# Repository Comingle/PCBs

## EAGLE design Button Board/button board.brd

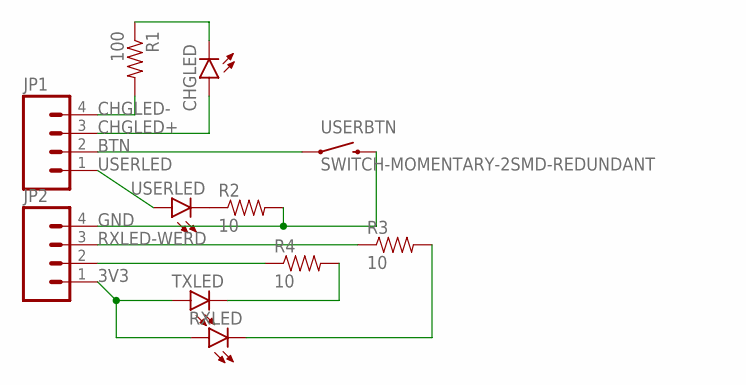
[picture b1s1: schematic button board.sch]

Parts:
CHGLED: LED-FKIT-1206; FKIT-LED-1206
JP1, JP2: M04PTH; 1X04
R1: 100; 0603-RES
R2, R3, R4: 10; 0603-RES
RXLED: LED-FKIT-1206; FKIT-LED-1206
TXLED: LED-FKIT-1206; FKIT-LED-1206
USERBTN: SWITCH-MOMENTARY-2SMD-REDUNDANT; TACTILE-SWITCH-SMD
USERLED: LED-FKIT-1206; FKIT-LED-1206

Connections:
3V3: JP2.1, RXLED.A, TXLED.A
BTN: JP1.2, USERBTN.1, USERBTN.2 (1)
CHGLED+: CHGLED.A, JP1.3
CHGLED-: JP1.4, R1.2
GND: JP2.4, R2.2, USERBTN.3 (2), USERBTN.4 (2)
unnamed: CHGLED.C, R1.1
unnamed: R2.1, USERLED.C
RXLED-: JP2.3, R3.1
RXLED-WERD: R3.2, RXLED.C
TXLED-: JP2.2, R4.1
TXLED-WERD: R4.2, TXLED.C
USERLED: JP1.1, USERLED.A

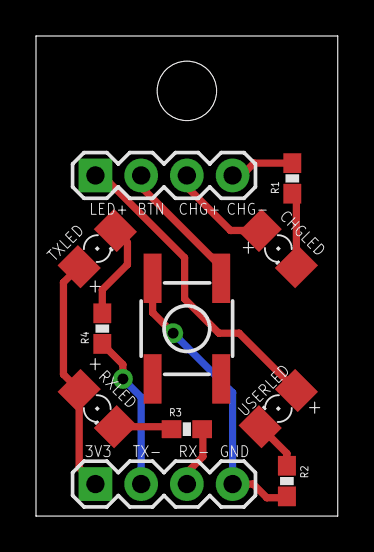
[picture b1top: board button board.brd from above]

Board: 2 copper layers, 16.8 x 26.7 mm, 12 parts (0 on the bottom side), 12 nets.

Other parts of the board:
U$1: STAND-OFF

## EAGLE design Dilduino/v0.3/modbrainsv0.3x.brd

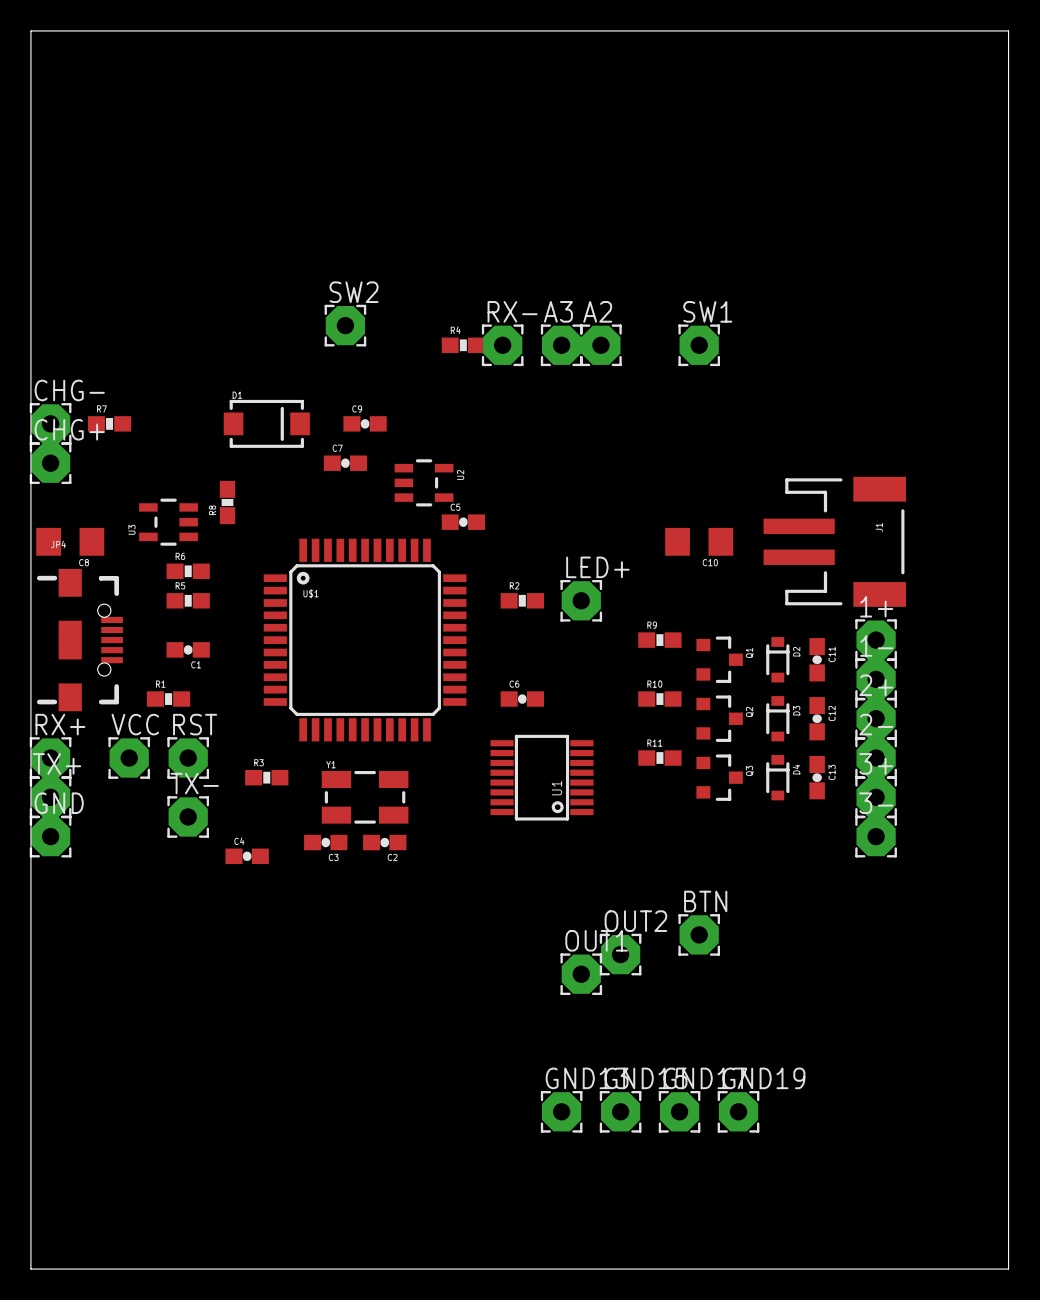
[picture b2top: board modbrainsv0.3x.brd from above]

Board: 2 copper layers, 63.2 x 80.0 mm, 66 parts (0 on the bottom side), 45 nets, no tracks yet.

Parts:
1+, 1-, 2+, 2-, 3+, 3-: 2,54/1,1
A2, A3: 2,54/1,1
BTN: 2,54/1,1
C1: 1.0uF; 0603-CAP
C2, C3: 22pF; 0603-CAP
C4, C5, C6, C11, C12, C13: 0.1uF; 0603-CAP
C7: 4.7uF; 0603-CAP
C8, C10: 4.7uF; 1206
C9: 470pF; 0603-CAP
CHG+: 2,54/1,1
CHG-: 2,54/1,1
D1: B340A; SMA-DIODE
D2, D3: BAT20JFILM; SOD-323
D4: 1N914BWS; SOD-323
FRAME1: FRAME-LETTER; CREATIVE_COMMONS
GND, GND13, GND15, GND17, GND19: 2,54/1,1
J1: JST-2-SMD
JP4: USB; USB-B-MICRO-SMD_V03
LED+: 2,54/1,1
OUT1, OUT2: 2,54/1,1
Q1, Q2, Q3: SOT23-3
R1, R8: 10k; 0603-RES
R2, R3, R4, R7: 430; 0603-RES
R5, R6: 22; 0603-RES
R9, R10, R11: 1k; 0603-RES
RST: 2,54/1,1
RX+: 2,54/1,1
RX-: 2,54/1,1
SW1, SW2: 2,54/1,1
TX+: 2,54/1,1
TX-: 2,54/1,1
U1: 74CBTLV3253; SSOP16-PRACTICE
U2: MIC5219 3.3V; SOT23-5
U3: MCP73831; SOT23-5
U$1: ATMEGA32U4TQFP-44; TQFP44
VCC: 2,54/1,1
Y1: CRYSTAL-SMD-5X3

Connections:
3.3V: RX+.1, TX+.1, U2.5, VCC.1
A7: U1.6, U$1.27
A8: U1.10, U$1.29
BVCC: 1+.1, 2+.1, 3+.1, C10.1, C11.1, C12.1, C13.1, D1.A, D2.C, D3.C, D4.C, J1.2, U3.3
D+: R6.2, U$1.4
D-: R5.2, U$1.3
GND: C1.2, C2.1, C3.1, C4.2, C5.2, C6.2, C7.2, C8.2, C9.2, C10.2, GND.1, GND13.1, GND15.1, GND17.1, GND19.1, J1.1, JP4.GND1, Q1.2, Q2.2, Q3.2, U1.1, U1.8, U1.15, U$1.5, U$1.15, U$1.23, U$1.33, U$1.35, U$1.43
MISO: U1.12, U$1.11
MOTOR1: R9.1, U$1.31
MOTOR2: R10.1, U$1.30
MOTOR3: R11.1, U$1.12
MUX0: U1.14, U$1.28
MUX1: U1.2, U$1.26
unnamed: C2.2, U$1.17, Y1.3
unnamed: C3.2, U$1.16, Y1.1
unnamed: R1.2, RST.1, U$1.13
unnamed: R2.1, U$1.32
unnamed: R4.1, U$1.8
unnamed: R3.1, U$1.22
unnamed: LED+.1, R2.2
unnamed: R4.2, RX-.1
unnamed: R3.2, TX-.1
unnamed: JP4.D+1, R5.1
unnamed: JP4.D-1, R6.1
unnamed: OUT2.1, U1.9
unnamed: OUT1.1, U1.7
unnamed: A2.1, U$1.38
unnamed: A3.1, U$1.39
unnamed: BTN.1, U$1.25
unnamed: R7.1, U3.1
unnamed: CHG-.1, R7.2
unnamed: R8.2, U2.2, U3.2
unnamed: SW2.1, U2.3
unnamed: C9.1, U2.4
unnamed: 1-.1, C11.2, D2.A, Q1.3
unnamed: 2-.1, C12.2, D3.A, Q2.3
unnamed: 3-.1, C13.2, D4.A, Q3.3
unnamed: Q1.1, R9.2
unnamed: Q2.1, R10.2
unnamed: Q3.1, R11.2
SCK: U1.4, U$1.9
SCL: U1.11, U$1.18
SDA: U1.5, U$1.19
UVCC: C8.1, CHG+.1, D1.C, JP4.VBUS1, SW1.1, U2.1, U3.4, U$1.7
VCC: C1.1, C4.1, C5.1, C6.1, C7.1, R1.1, U1.16, U$1.6, U$1.14, U$1.24, U$1.34, U$1.42, U$1.44

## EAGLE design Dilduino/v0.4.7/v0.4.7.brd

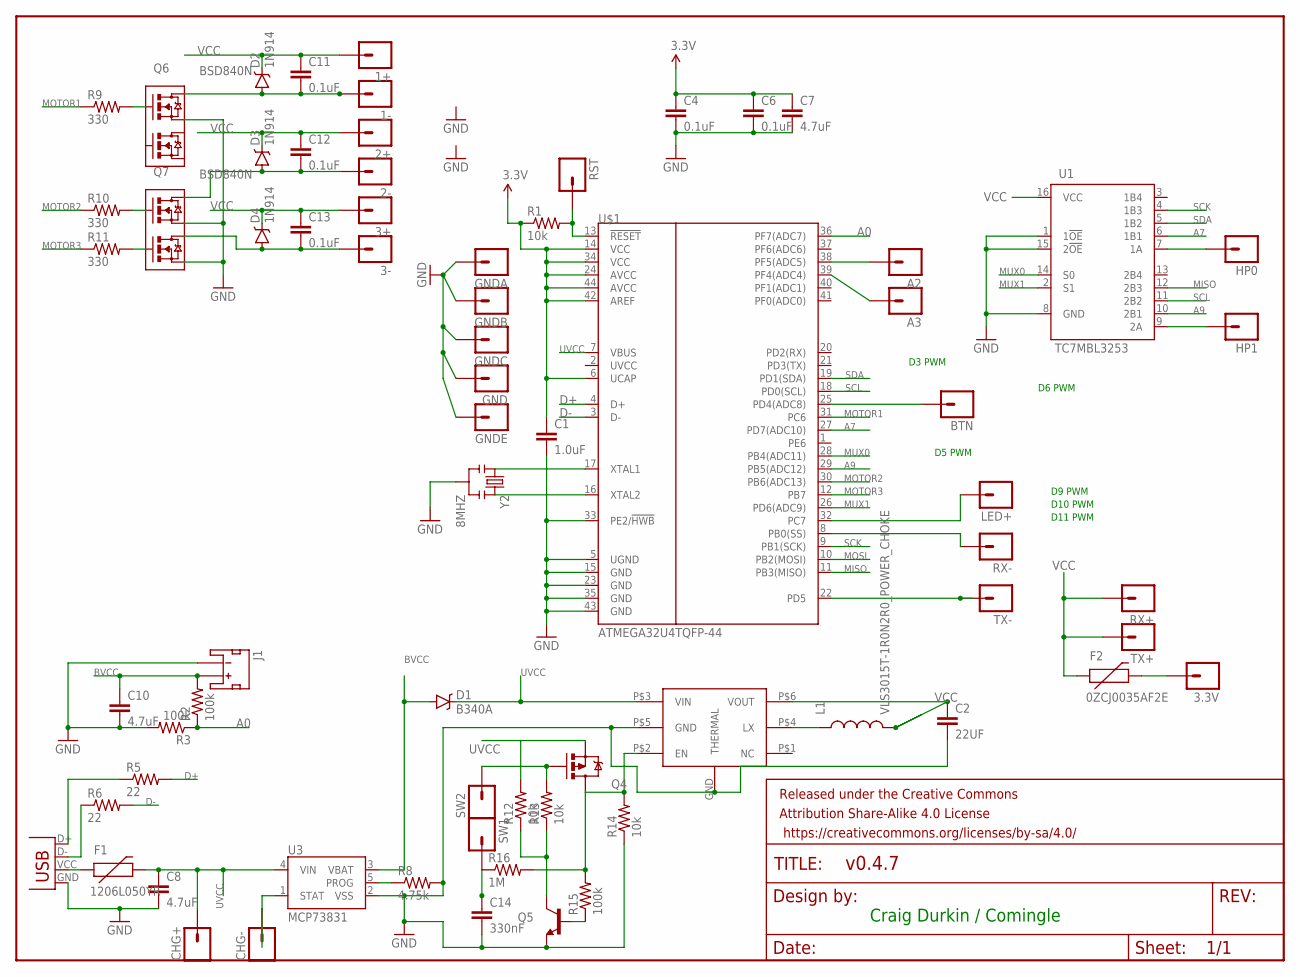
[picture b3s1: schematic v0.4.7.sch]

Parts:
1+, 1-, 2+, 2-, 3+, 3-, 3.3V: M01PTH; 1X01
A2, A3: M01PTH; 1X01
BTN: M01PTH; 1X01
C1: 1.0uF; 0603-CAP
C2: 22UF; 0805
C4, C6, C11, C12, C13: 0.1uF; 0603-CAP
C7: 4.7uF; 0603-CAP
C8, C10: 4.7uF; 1206
C14: 330nF; 0603-CAP
CHG+: M01PTH; 1X01
CHG-: M01PTH; 1X01
D1: B340A; SMA-DIODE
D2, D3, D4: 1N914; SOD-323
F1: 1206L050YR; PTC-1206
F2: 0ZCJ0035AF2E; PTC-1206
FRAME1: FRAME-LETTER; CREATIVE_COMMONS
GND: M01PTH; 1X01
GNDA: M01PTH; 1X01
GNDB: M01PTH; 1X01
GNDC: M01PTH; 1X01
GNDE: M01PTH; 1X01
HP0, HP1: M01PTH; 1X01
J1: JST_2MM_MALE; JST-2-SMD
JP4: USBMICROB-GCT-USB3075; USB-MICROB-GCT-USB3075
L1: VLS3015T-1R0N2R0_POWER_CHOKE; 3MM_POWER_CHOKE
LED+: M01PTH; 1X01
Q4: NTS2101PT1G; SOT23-3
Q5: MMBT2222A; SOT23-3
Q6, Q7: BSD840N; PG-SOT-363
R1, R12, R13, R14: 10k; 0603-RES
R2, R3, R15: 100k; 0603-RES
R5, R6: 22; 0603-RES
R8: 4.75k; 0603-RES
R9, R10, R11: 330; 0603-RES
R16: 1M; 0603-RES
RST: M01PTH; 1X01
RX+: M01PTH; 1X01
RX-: M01PTH; 1X01
SW1, SW2: M01PTH; 1X01
TX+: M01PTH; 1X01
TX-: M01PTH; 1X01
U1: TC7MBL3253; SSOP16-PRACTICE
U3: MCP73831; SOT23-5
U$1: ATMEGA32U4TQFP-44; TQFP44
U$3: SC189; MLPD-UT6
Y2: 8MHZ; RESONATOR-SMD

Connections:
A0: R2.1, R3.1, U$1.36 (PF7(ADC7))
A7: U1.6 (1B1), U$1.27 (PD7(ADC10))
A9: U1.10 (2B1), U$1.29 (PB5(ADC12))
BVCC: C10.1, D1.A, J1.2 (+), R2.2, U3.3 (VBAT)
D+: R5.2, U$1.4 (D+)
D-: R6.2, U$1.3 (D-)
GND: C1.2, C2.2, C4.2, C6.2, C7.2, C8.2, C10.2, C14.2, GND.1, GNDA.1, GNDB.1, GNDC.1, GNDE.1, J1.1 (-), JP4.GND, Q5.2 (E), Q6.1 (S), Q7.1 (S), Q7.4 (S1), R3.2, R8.2, R14.1, U1.1 (1!OE), U1.8 (GND), U1.15 (2!OE), U3.2 (VSS), U$1.5 (UGND), U$1.15 (GND), U$1.23 (GND), U$1.33 (PE2/!HWB), U$1.35 (GND), U$1.43 (GND), U$3.GND (THERMAL), U$3.P$5 (GND), Y2.2
MISO: U1.12 (2B3), U$1.11 (PB3(MISO))
MOSI: U$1.10 (PB2(MOSI))
MOTOR1: R9.1, U$1.31 (PC6)
MOTOR2: R10.1, U$1.30 (PB6(ADC13))
MOTOR3: R11.1, U$1.12 (PB7)
MUX0: U1.14 (S0), U$1.28 (PB4(ADC11))
MUX1: U1.2 (S1), U$1.26 (PD6(ADC9))
unnamed: U$1.17 (XTAL1), Y2.1
unnamed: R8.1, U3.5 (PROG)
unnamed: F1.1, JP4.VCC (VBUS)
unnamed: 3.3V.1, F2.2
unnamed: U$1.16 (XTAL2), Y2.3
unnamed: LED+.1, U$1.32 (PC7)
unnamed: RX-.1, U$1.8 (PB0(SS))
unnamed: TX-.1, U$1.22 (PD5)
unnamed: JP4.D+, R5.1
unnamed: JP4.D-, R6.1
unnamed: L1.1, U$3.P$4 (LX)
unnamed: HP1.1, U1.9 (2A)
unnamed: HP0.1, U1.7 (1A)
unnamed: A2.1, U$1.38 (PF5(ADC5))
unnamed: A3.1, U$1.39 (PF4(ADC4))
unnamed: BTN.1, U$1.25 (PD4(ADC8))
unnamed: CHG-.1, U3.1 (STAT)
unnamed: Q5.3 (C), R12.1, R13.1
unnamed: C14.1, R16.1, SW1.1
unnamed: Q4.1 (G), R13.2, SW2.1
unnamed: 1-.1, C11.2, D2.A, Q6.6 (D)
unnamed: 2-.1, C12.2, D3.A, Q7.6 (D)
unnamed: 3-.1, C13.2, D4.A, Q7.3 (D1)
unnamed: Q5.1 (B), R15.1
REG_ENBL: Q4.3 (D), R14.2, R15.2, R16.2, U$3.P$2 (EN)
RST: R1.2, RST.1, U$1.13 (!RESET)
SCK: U1.4 (1B3), U$1.9 (PB1(SCK))
SCL: U1.11 (2B2), U$1.18 (PD0(SCL))
SDA: U1.5 (1B2), U$1.19 (PD1(SDA))
UVCC: C8.1, CHG+.1, D1.C, F1.2, Q4.2 (S), R12.2, U3.4 (VIN), U$1.7 (VBUS), U$3.P$3 (VIN)
VCC: 1+.1, 2+.1, 3+.1, C1.1, C2.1, C4.1, C6.1, C7.1, C11.1, C12.1, C13.1, D2.C, D3.C, D4.C, F2.1, L1.2, R1.1, RX+.1, TX+.1, U1.16 (VCC), U$1.6 (UCAP), U$1.14 (VCC), U$1.24 (AVCC), U$1.34 (VCC), U$1.42 (AREF), U$1.44 (AVCC), U$3.P$6 (VOUT)

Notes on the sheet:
Craig Durkin / Comingle
D3 PWM
D5 PWM
D6 PWM
D9 PWM
D10 PWM
D11 PWM

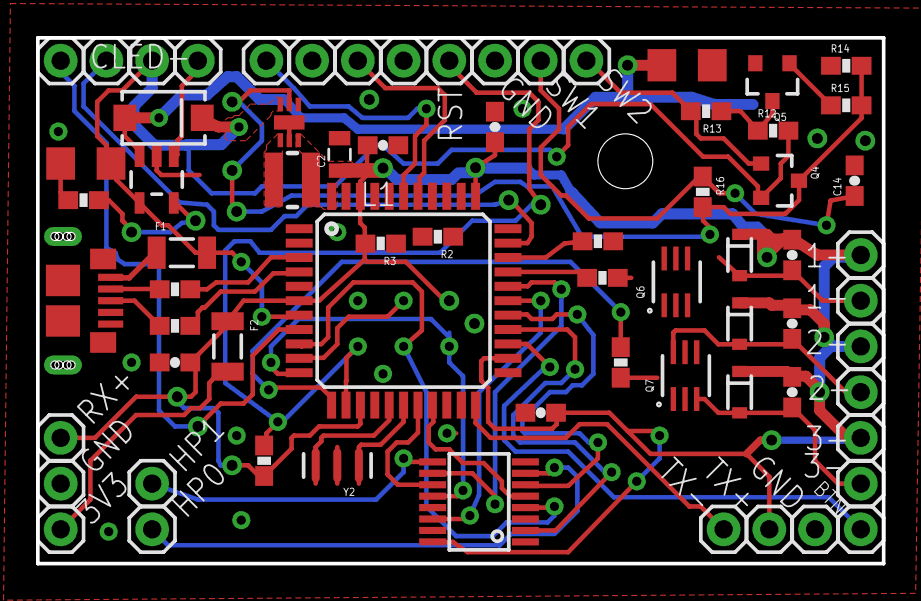
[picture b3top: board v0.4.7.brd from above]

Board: 2 copper layers, 47.0 x 29.2 mm, 72 parts (1 on the bottom side), 44 nets.

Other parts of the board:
U$2: STAND-OFF-TIGHT

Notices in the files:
parts and their libraries:
SparkFun-LED: Licensing: Creative Commons ShareAlike 4.0 International - https://creativecommons.org/licenses/by-sa/4.0
SparkFun-Aesthetics: Released under the Creative Commons Attribution Share-Alike 4.0 License
SparkFun-Aesthetics: https://creativecommons.org/licenses/by-sa/4.0
